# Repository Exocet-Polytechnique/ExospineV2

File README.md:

# ExoSpineV2
Version 2 of the PCB.

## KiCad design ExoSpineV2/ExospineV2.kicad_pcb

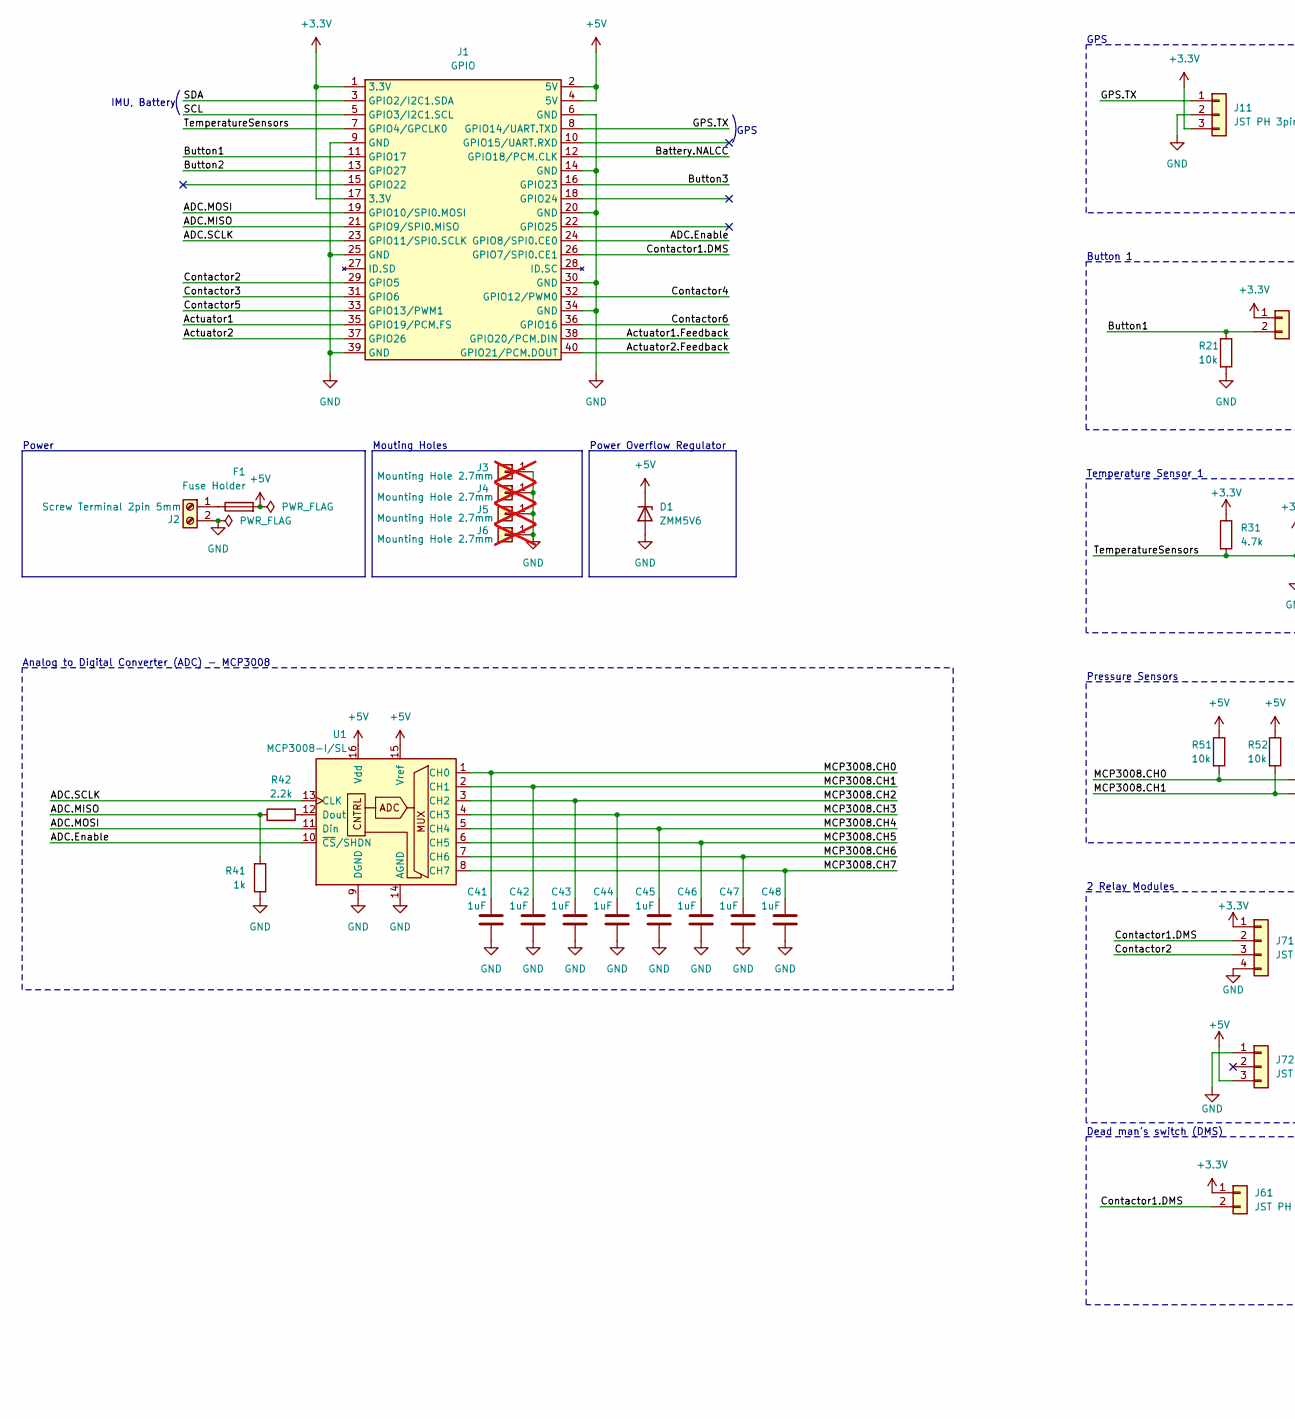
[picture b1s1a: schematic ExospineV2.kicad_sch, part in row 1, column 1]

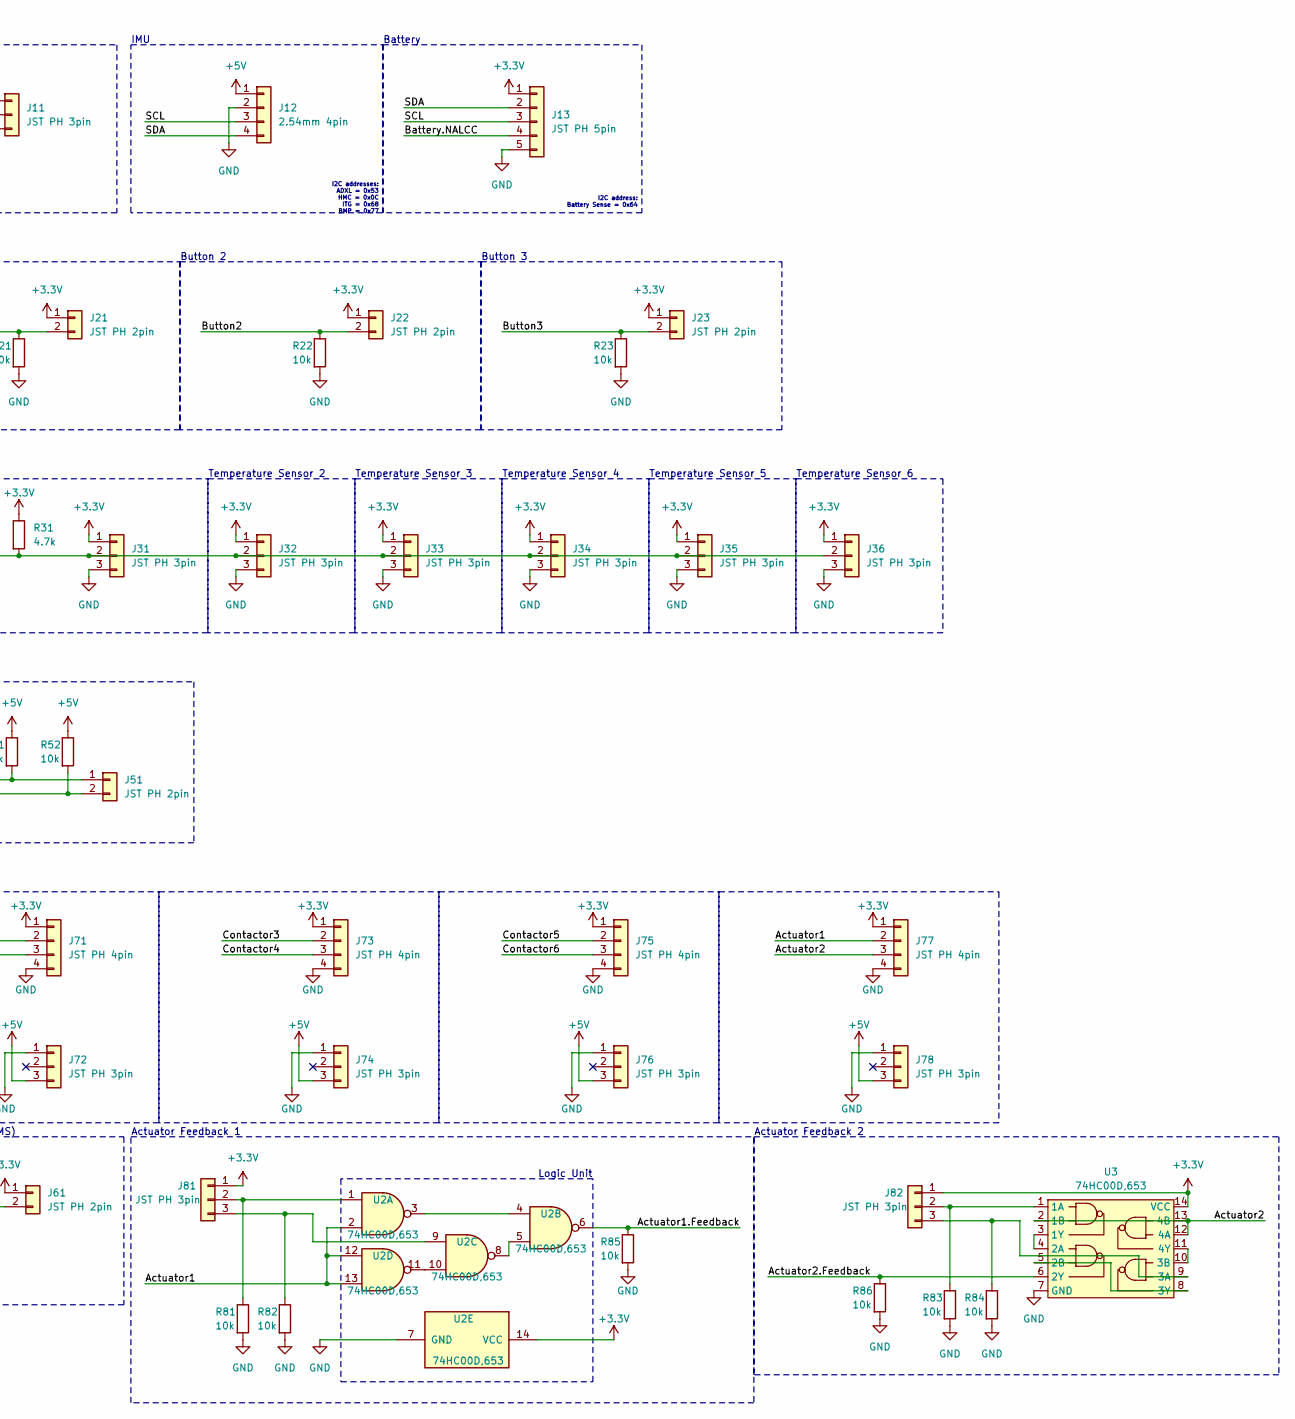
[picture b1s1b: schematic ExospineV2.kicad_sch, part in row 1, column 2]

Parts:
C41, C42, C43, C44, C45, C46, C47, C48: 1uF; C_0402_1005Metric; JLCPCB Part Number C52923
D1: ZMM5V6; D_MiniMELF; JLCPCB Part Number C5345993
F1: Fuse Holder; [Mouser~]01530008(Littelfuse); JLCPCB Part Number C206907
J1: GPIO; PinSocket_2x20_P2.54mm_Vertical; JLCPCB Part Number C2977589
J2: Screw Terminal 2pin 5mm; [Exocet]MX126-5.0-02P-GN01-Cu-S-A; JLCPCB Part Number C5188434
J3, J4, J5, J6: Mounting Hole 2.7mm; MountingHole_2.7mm_Pad; not fitted
J11, J31, J32, J33, J34, J35, J36, J72, J74, J76, J78, J81, J82: JST PH 3pin; JST_PH_B3B-PH-K_1x03_P2.00mm_Vertical; JLCPCB Part Number C131339
J12: 2.54mm 4pin; PinHeader_1x04_P2.54mm_Vertical; JLCPCB Part Number C5116483
J13: JST PH 5pin; JST_PH_B5B-PH-K_1x05_P2.00mm_Vertical; JLCPCB Part Number C157993
J21, J22, J23, J51, J61: JST PH 2pin; JST_PH_B2B-PH-K_1x02_P2.00mm_Vertical; JLCPCB Part Number C131337
J71, J73, J75, J77: JST PH 4pin; JST_PH_B4B-PH-K_1x04_P2.00mm_Vertical; JLCPCB Part Number C131334
R21, R22, R23, R51, R52, R81, R82, R83, R84, R85, R86: 10k; R_0402_1005Metric; JLCPCB Part Number C25744
R31: 4.7k; R_0402_1005Metric; JLCPCB Part Number C25900
R41: 1k; R_0402_1005Metric; JLCPCB Part Number C11702
R42: 2.2k; R_0402_1005Metric; JLCPCB Part Number C25879
U1: MCP3008-I/SL; SOIC-16_3.9x9.9mm_P1.27mm; JLCPCB Part Number C1520159
U2, U3: 74HC00D,653; SOIC-14_3.9x8.7mm_P1.27mm; JLCPCB Part Number C5586

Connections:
+3.3V: J1.1 (3.3V), J1.17 (3.3V), J11.3, J13.1, J21.1, J22.1, J23.1, J31.1, J32.1, J33.1, J34.1, J35.1, J36.1, J61.1, J71.1, J73.1, J75.1, J77.1, J81.1, J82.1, R31.1, U2.14 (VCC), U3.14 (VCC)
+5V: D1.1 (K), F1.2, J1.2 (5V), J1.4 (5V), J12.1, J72.3, J74.3, J76.3, J78.3, R51.1, R52.1, U1.15 (Vref), U1.16 (Vdd)
/ADC.Enable: J1.24 (GPIO8/SPI0.CE0), U1.10 (~CS/SHDN)
/ADC.MISO: J1.21 (GPIO9/SPI0.MISO), R41.2, R42.1
/ADC.MOSI: J1.19 (GPIO10/SPI0.MOSI), U1.11 (Din)
/ADC.SCLK: J1.23 (GPIO11/SPI0.SCLK), U1.13 (CLK)
/Actuator1: J1.35 (GPIO19/PCM.FS), J77.2, U2.2, U2.12, U2.13
/Actuator1.Feedback: J1.38 (GPIO20/PCM.DIN), R85.1, U2.6
/Actuator2: J1.37 (GPIO26), J77.3, U3.2 (1B), U3.12 (4A), U3.13 (4B)
/Actuator2.Feedback: J1.40 (GPIO21/PCM.DOUT), R86.1, U3.6 (2Y)
/Battery.NALCC: J1.12 (GPIO18/PCM.CLK), J13.4
/Button1: J1.11 (GPIO17), J21.2, R21.1
/Button2: J1.13 (GPIO27), J22.2, R22.1
/Button3: J1.16 (GPIO23), J23.2, R23.1
/Contactor1.DMS: J1.26 (GPIO7/SPI0.CE1), J61.2, J71.2
/Contactor2: J1.29 (GPIO5), J71.3
/Contactor3: J1.31 (GPIO6), J73.2
/Contactor4: J1.32 (GPIO12/PWM0), J73.3
/Contactor5: J1.33 (GPIO13/PWM1), J75.2
/Contactor6: J1.36 (GPIO16), J75.3
/GPS.TX: J1.8 (GPIO14/UART.TXD), J11.1
/MCP3008.CH0: C41.1, J51.1, R51.2, U1.1 (CH0)
/MCP3008.CH1: C42.1, J51.2, R52.2, U1.2 (CH1)
/MCP3008.CH2: C43.1, U1.3 (CH2)
/MCP3008.CH3: C44.1, U1.4 (CH3)
/MCP3008.CH4: C45.1, U1.5 (CH4)
/MCP3008.CH5: C46.1, U1.6 (CH5)
/MCP3008.CH6: C47.1, U1.7 (CH6)
/MCP3008.CH7: C48.1, U1.8 (CH7)
/SCL: J1.5 (GPIO3/I2C1.SCL), J12.3, J13.3
/SDA: J1.3 (GPIO2/I2C1.SDA), J12.4, J13.2
/TemperatureSensors: J1.7 (GPIO4/GPCLK0), J31.2, J32.2, J33.2, J34.2, J35.2, J36.2, R31.2
GND: C41.2, C42.2, C43.2, C44.2, C45.2, C46.2, C47.2, C48.2, D1.2 (A), J1.6 (GND), J1.9 (GND), J1.14 (GND), J1.20 (GND), J1.25 (GND), J1.30 (GND), J1.34 (GND), J1.39 (GND), J2.2, J3.1, J4.1, J5.1, J6.1, J11.2, J12.2, J13.5, J31.3, J32.3, J33.3, J34.3, J35.3, J36.3, J71.4, J72.1, J73.4, J74.1, J75.4, J76.1, J77.4, J78.1, R21.2, R22.2, R23.2, R41.1, R81.2, R82.2, R83.2, R84.2, R85.2, R86.2, U1.9 (DGND), U1.14 (AGND), U2.7 (GND), U3.7 (GND)
unnamed: F1.1, J2.1
unnamed: J81.2, R81.1, U2.1
unnamed: J81.3, R82.1, U2.9
unnamed: J82.2, R83.1, U3.1 (1A)
unnamed: J82.3, R84.1, U3.9 (3A)
unnamed: R42.2, U1.12 (Dout)
unnamed: U2.3, U2.4
unnamed: U2.5, U2.8
unnamed: U2.10, U2.11
unnamed: U3.3 (1Y), U3.4 (2A)
unnamed: U3.5 (2B), U3.8 (3Y)
unnamed: U3.10 (3B), U3.11 (4Y)

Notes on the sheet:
I2C address: Battery Sense = 0x64
I2C addresses: ADXL = 0x53 HMC = 0x0C ITG = 0x68 BMP = 0x77
Actuator Feedback 1
IMU, Battery
Button 3
Mouting Holes
Power Overflow Regulator
Temperature Sensor 6
2 Relay Modules
Battery
Temperature Sensor 1
IMU
Power
Button 2
GPS
Temperature Sensor 3
Pressure Sensors
Actuator Feedback 2
Button 1
Logic Unit
Analog to Digital Converter (ADC) - MCP3008
Temperature Sensor 5
Temperature Sensor 2
Temperature Sensor 4
Dead man's switch (DMS)

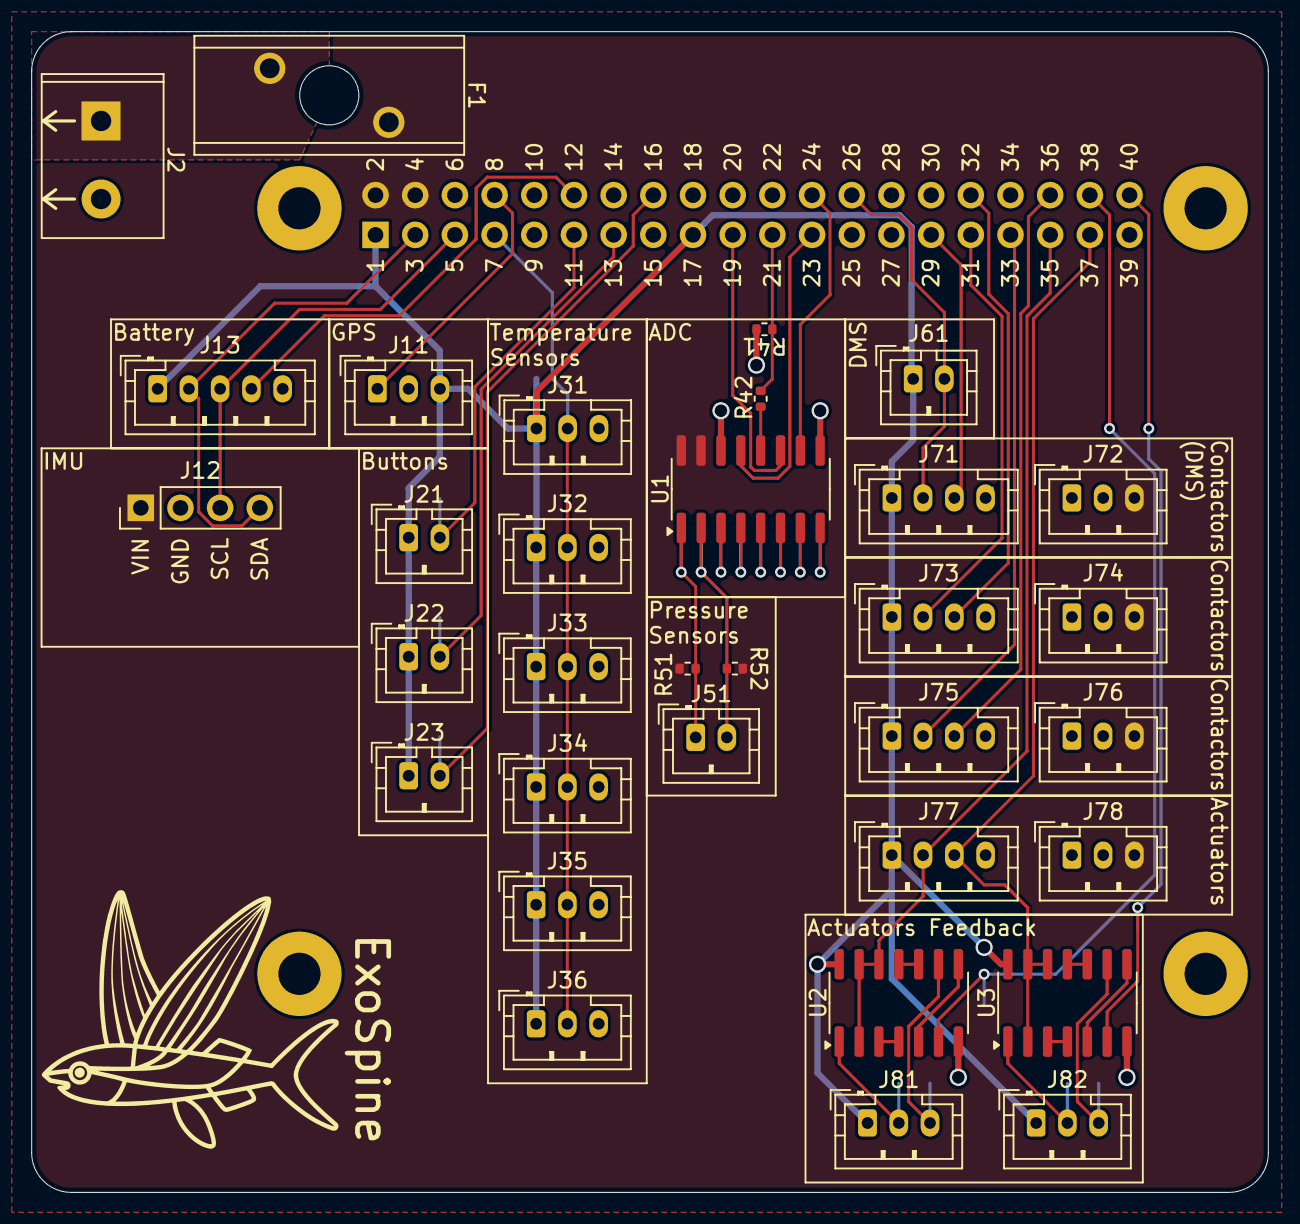
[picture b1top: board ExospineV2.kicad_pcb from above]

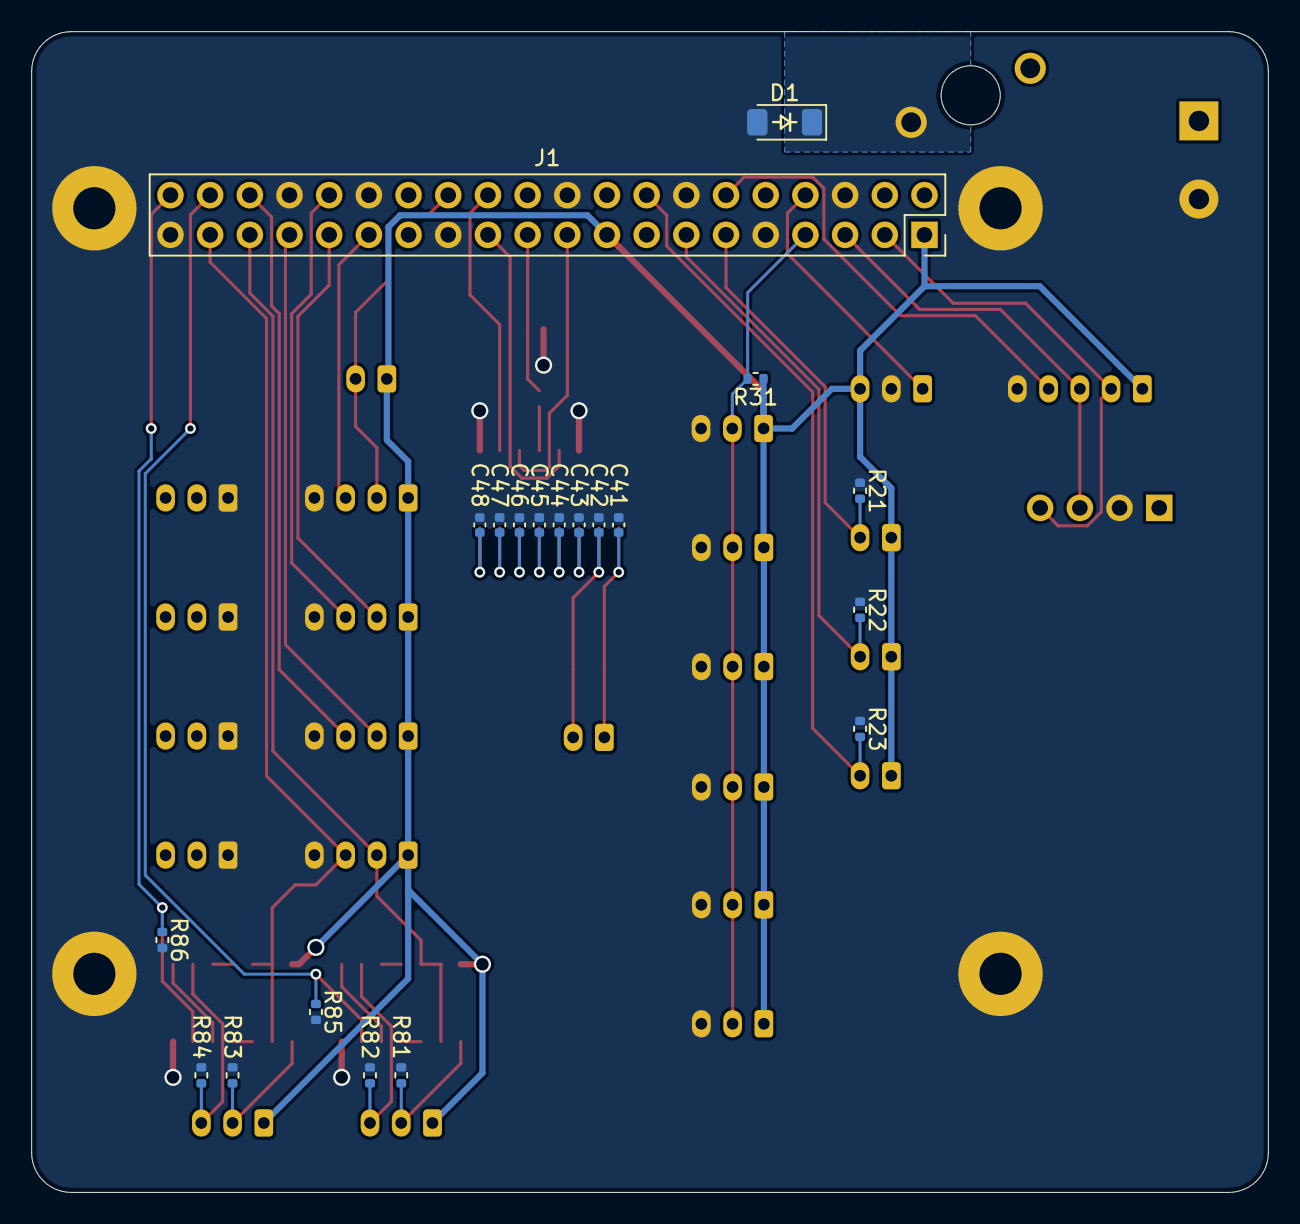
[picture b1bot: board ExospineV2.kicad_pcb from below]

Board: 2 copper layers, 79.2 x 74.3 mm, 57 parts (20 on the bottom side), 45 nets.

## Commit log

2024-01-26 Minor changes
2024-01-26 test
2024-01-26 Ajout de pin assignment du Raspberry Pi
2024-01-28 ajouté des noms au Raspberry
2024-01-28 Remove KiCad-generated files
2024-01-28 Add gitignore
2024-01-28 Move projet to root directory (rebase from main)
2024-01-28 Update gitignore
2024-01-28 Ajout d'un raspberryPi modèle
2024-01-28 changement du schéma, ajout d'une thermistance (contact). Pas besoin d'en mettre plus mais bon exercice
2024-01-28 ajout
2024-01-28 Move files
2024-01-28 created MCP3008 and imported ExoSpineV1
2024-01-28 created CPU circuits
2024-01-29 ajout début alimentation 5v
2024-01-29 ajout des capteurs de pression (x3) et d'un peu d'info sur le dcdc12-5v
2024-01-30 probablement pas de grandes modifications
2024-01-30 ajout de condensateur de decouplage pour les thermistances
2024-01-30 jsp ce que j'ai fait mais j'ai avancé
2024-02-07 organized
2024-02-07 modified .gitignore
2024-02-07 Temperature Sensor 1
2024-02-09 Added actuators logic circuits
2024-02-09 modified actuators
2024-02-12 updated .gitignore
2024-02-12 Created `ElectricalLayout`
2024-02-13 MCP3008 circuit
2024-02-13 moved MCP3008_and_channels schematic to EletricLayout
2024-02-13 Actuator Control 1
2024-02-13 Actuator Control 2 and backup
2024-02-13 Identified RP pins
2024-02-13 Added 12V connector on PCB
2024-02-13 Added Pressure Sensors 1 and 2
2024-02-13 Added Pressure Sensor Backup
2024-02-13 Correction for Actuator Controls (12V down to 5V)
2024-02-13 Added Contactors 2 and 3
2024-02-13 Added Temperature Sensors
2024-02-13 Modified Logic Circuit for Actuators Feedback
2024-02-13 12v or 5v?
2024-02-13 Added logic circuit for actuators feedback
2024-02-14 petits changements
2024-02-14 normalement le merge est fait, faut que on travaille chaqu'un de son côté ou que on s'assure de truc genre Merge souvent pcq sinon ça part en couilles
2024-02-14 rajout de la fiche du convertisseur dc-dc buck converter qui baisse la tension pour alimenter le Pi
2024-02-14 Added I2C addresses
2024-02-15 Modified temperature sensors connectors
2024-02-22 planned mux and LTC2942
2024-03-05 added LTC4312 circuit
2024-03-05 Added connections to batteries PCBs
2024-03-05 added connection type for GPS
2024-03-21 added connectors
2024-03-21 modified battery feedback control (switch)
2024-03-27 generated PDF
2024-03-28 chose 10k resistors on JLCPCB (datasheets & footprints)
2024-03-29 chose resistors and capacitors
2024-04-01 dimensionnement des composantes pour le DC-DC
2024-04-04 ajout de composantes au board
2024-04-05 dimensionnage de certaines composantes
2024-04-05 changement de un peu de librairies de parts, finition du premier PCB
2024-04-05 Link de toutes les composantes à utiliser
2024-05-08 changed symbols
2024-05-08 removed LTC2944 (?) (bottom left of root page)
2024-05-08 changed actuator control circuit
2024-05-08 moved ExoSpineV1
2024-05-08 last commit before removing 12V-5V buck converter
2024-05-08 removed 12v-5v buck converter
2024-05-08 removed unused pages (ExoSpineV1 & LTC4312)
2024-05-09 9 mai 2024
2024-05-09 updated symbol fields in schematic
2024-05-10 started working on PCB
2024-05-10 organizing MCP3008 circuit
2024-05-11 last commit before removing old circuit for contactor & replacing it
2024-05-11 removed old circuit for contactors
2024-05-12 last commit before changing temperature sensors circuit
2024-05-13 positioned temperature sensors connectors on PCB
2024-05-13 last commit before removing circuit for LTC4312 (I2C Multiplexer)
2024-05-13 removed circuit for LTC4312 (I2C Multiplexer)
2024-05-13 updated pdf
2024-05-14 continued PCB
2024-05-15 changed actuator feedback circuit
2024-05-15 placed some components on PCB
2024-05-15 Kicad 8
2024-05-16 sized traces (Power/default)
2024-05-16 placed components on the left of the PCB and added traces
2024-05-16 places 5V power connector & traces
2024-05-17 added a 2 relay module
2024-05-17 removed Throttle circuits (pull-up & pull-down)
2024-05-19 updated footprints
2024-05-20 added power plane
2024-05-20 updated battery connector (ALCC)
2024-05-21 clarified net names among other things
2024-05-21 added footprints (Power)
2024-05-21 fixed some DRC errors
2024-05-21 little modifications
2024-05-21 chose all JLCPCB parts
2024-05-21 added resistors
2024-05-22 added resistors for actuators feedback
2024-05-22 fixed errors
2024-05-22 added graphics
2024-05-22 fixed problem with the screw terminal
2024-05-22 settings for fabrication outputs
2024-05-22 fixed pcb for gerber files
2024-05-23 generating files for order
2024-05-23 commit used for the JLCPCB order
